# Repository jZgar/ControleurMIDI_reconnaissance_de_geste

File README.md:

# ControleurMIDI_reconnaissance_de_geste
Projet de deuxième année - ENSEA

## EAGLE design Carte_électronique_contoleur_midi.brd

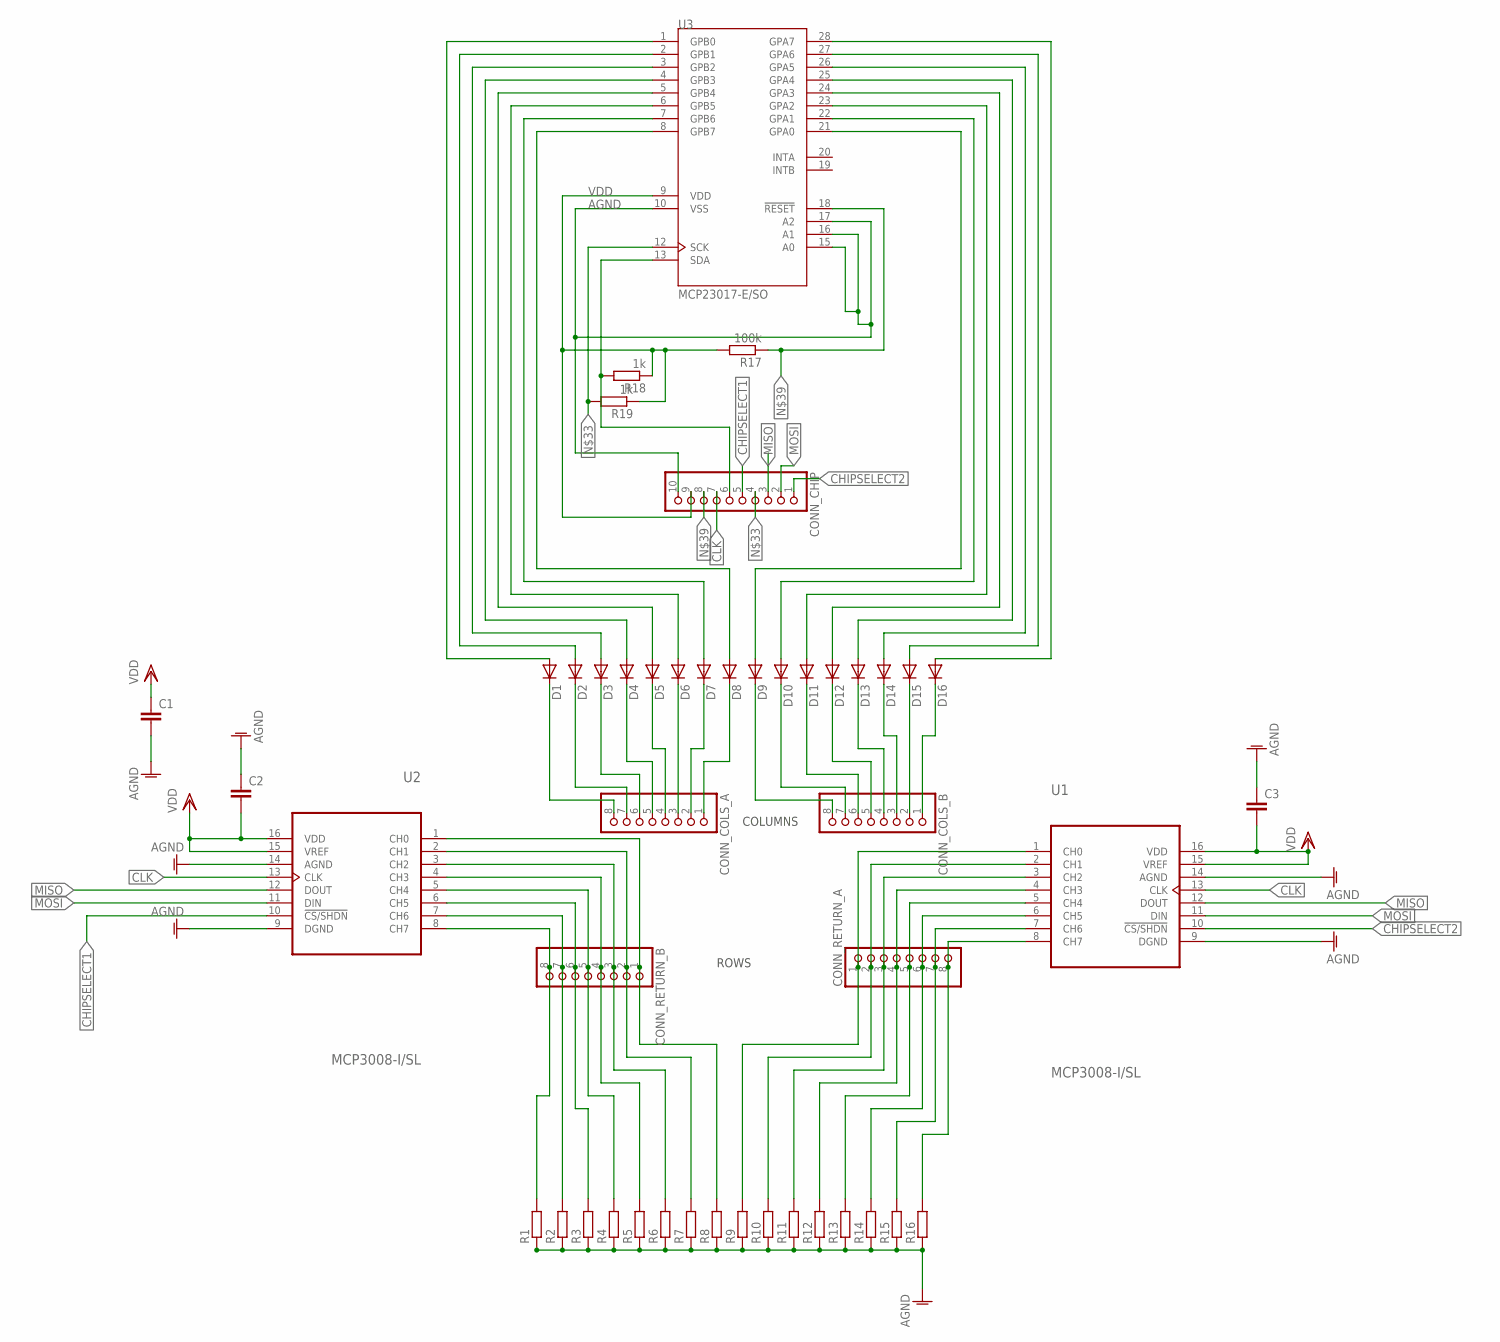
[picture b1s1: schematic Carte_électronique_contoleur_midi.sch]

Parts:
C1, C2, C3: C-EUC1206K; C1206K
CONN_CHIP: PINHD-1X10/90; 1X10/90
CONN_COLS_A: PINHD-1X8/90; 1X08/90
CONN_COLS_B: PINHD-1X8/90; 1X08/90
CONN_RETURN_A: PINHD-1X8/90; 1X08/90
CONN_RETURN_B: PINHD-1X8/90; 1X08/90
D1, D2, D3, D4, D5, D6, D7, D8, D9, D10, D11, D12, D13, D14, D15, D16: DIODE-SOD323-W; SOD323-W
R1, R2, R3, R4, R5, R6, R7, R8, R9, R10, R11, R12, R13, R14, R15, R16: R-EU_M1206; M1206
R17: 100k; M1206
R18, R19: 1k; M1206
U1, U2: MCP3008-I/SL; SOIC127P600X175-16N
U3: MCP23017-E/SO; SOIC127P1030X265-28N

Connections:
AGND: C1.2, C2.1, C3.1, CONN_CHIP.10, R1.1, R2.1, R3.1, R4.1, R5.1, R6.1, R7.1, R8.1, R9.1, R10.1, R11.1, R12.1, R13.1, R14.1, R15.1, R16.1, U1.9 (DGND), U1.14 (AGND), U2.9 (DGND), U2.14 (AGND), U3.10 (VSS), U3.15 (A0), U3.16 (A1), U3.17 (A2)
CHIPSELECT1: CONN_CHIP.5, U2.10 (!CS/SHDN)
CHIPSELECT2: CONN_CHIP.1, U1.10 (!CS/SHDN)
CLK: CONN_CHIP.7, U1.13 (CLK), U2.13 (CLK)
MISO: CONN_CHIP.3, U1.12 (DOUT), U2.12 (DOUT)
MOSI: CONN_CHIP.2, U1.11 (DIN), U2.11 (DIN)
unnamed: D8.A, U3.8 (GPB7)
unnamed: D7.A, U3.7 (GPB6)
unnamed: D6.A, U3.6 (GPB5)
unnamed: D5.A, U3.5 (GPB4)
unnamed: D4.A, U3.4 (GPB3)
unnamed: D3.A, U3.3 (GPB2)
unnamed: D2.A, U3.2 (GPB1)
unnamed: D1.A, U3.1 (GPB0)
unnamed: D9.A, U3.21 (GPA0)
unnamed: D10.A, U3.22 (GPA1)
unnamed: D11.A, U3.23 (GPA2)
unnamed: D12.A, U3.24 (GPA3)
unnamed: D13.A, U3.25 (GPA4)
unnamed: D14.A, U3.26 (GPA5)
unnamed: D15.A, U3.27 (GPA6)
unnamed: D16.A, U3.28 (GPA7)
unnamed: CONN_COLS_A.8, D1.C
unnamed: CONN_COLS_A.7, D2.C
unnamed: CONN_COLS_A.6, D3.C
unnamed: CONN_COLS_A.5, D4.C
unnamed: CONN_COLS_A.4, D5.C
unnamed: CONN_COLS_A.3, D6.C
unnamed: CONN_COLS_A.2, D7.C
unnamed: CONN_COLS_A.1, D8.C
unnamed: CONN_COLS_B.8, D9.C
unnamed: CONN_COLS_B.7, D10.C
unnamed: CONN_COLS_B.6, D11.C
unnamed: CONN_COLS_B.5, D12.C
unnamed: CONN_COLS_B.4, D13.C
unnamed: CONN_COLS_B.3, D14.C
unnamed: CONN_COLS_B.2, D15.C
unnamed: CONN_COLS_B.1, D16.C
unnamed: CONN_CHIP.4, R19.2, U3.12 (SCK)
unnamed: CONN_CHIP.6, R18.2, U3.13 (SDA)
unnamed: CONN_CHIP.8, R17.1, U3.18 (!RESET)
unnamed: CONN_RETURN_B.1, R8.2, U2.1 (CH0)
unnamed: CONN_RETURN_B.2, R7.2, U2.2 (CH1)
unnamed: CONN_RETURN_B.3, R6.2, U2.3 (CH2)
unnamed: CONN_RETURN_B.5, R4.2, U2.5 (CH4)
unnamed: CONN_RETURN_B.6, R3.2, U2.6 (CH5)
unnamed: CONN_RETURN_B.7, R2.2, U2.7 (CH6)
unnamed: CONN_RETURN_B.8, R1.2, U2.8 (CH7)
unnamed: CONN_RETURN_A.2, R10.2, U1.2 (CH1)
unnamed: CONN_RETURN_A.3, R11.2, U1.3 (CH2)
unnamed: CONN_RETURN_A.4, R12.2, U1.4 (CH3)
unnamed: CONN_RETURN_A.1, R9.2, U1.1 (CH0)
unnamed: CONN_RETURN_A.5, R13.2, U1.5 (CH4)
unnamed: CONN_RETURN_A.6, R14.2, U1.6 (CH5)
unnamed: CONN_RETURN_A.7, R15.2, U1.7 (CH6)
unnamed: CONN_RETURN_A.8, R16.2, U1.8 (CH7)
unnamed: CONN_RETURN_B.4, R5.2, U2.4 (CH3)
VDD: C1.1, C2.2, C3.2, CONN_CHIP.9, R17.2, R18.1, R19.1, U1.15 (VREF), U1.16 (VDD), U2.15 (VREF), U2.16 (VDD), U3.9 (VDD)

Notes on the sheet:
COLUMNS
ROWS

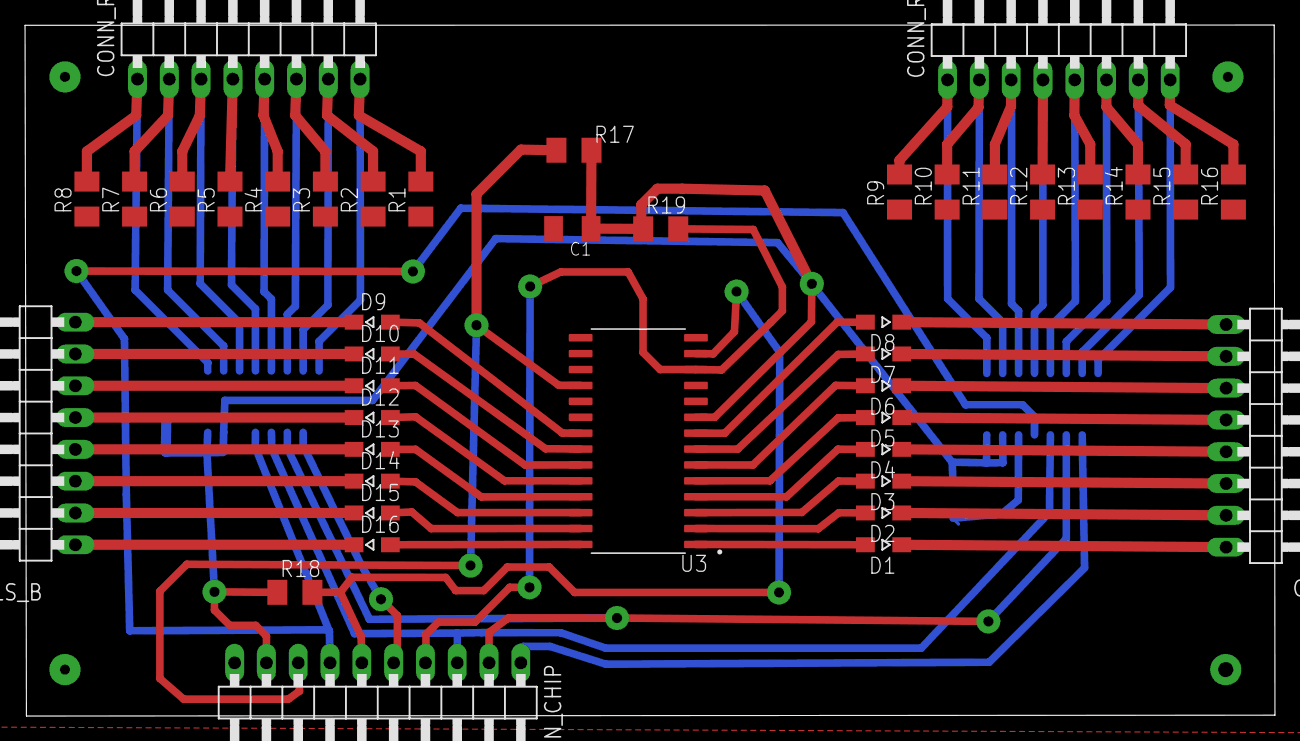
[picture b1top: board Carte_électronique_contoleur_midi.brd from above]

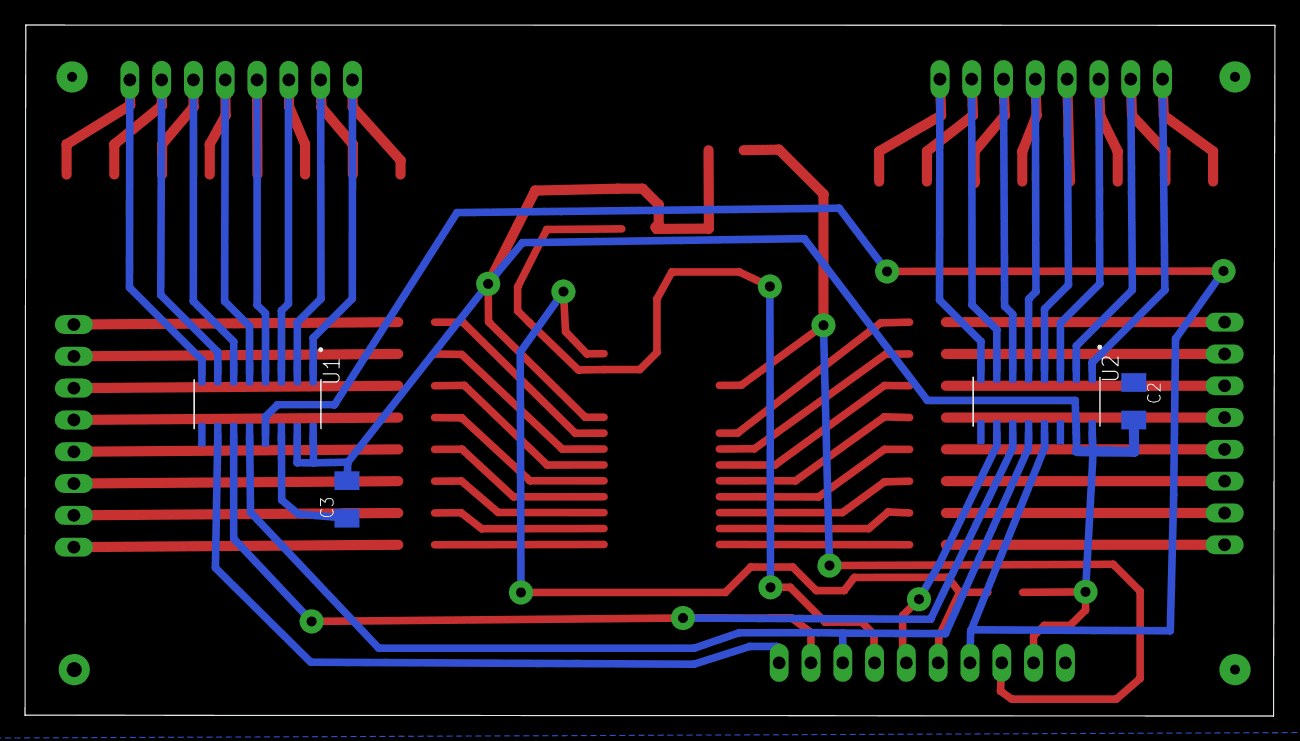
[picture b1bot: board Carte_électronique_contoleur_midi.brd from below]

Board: 2 copper layers, 99.8 x 55.2 mm, 46 parts (4 on the bottom side), 58 nets.

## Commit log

2022-04-22 Create test
2022-04-22 Create controllerMIDI.h5
    IA entraînée
2022-04-22 Update controllermidi_py.py
    Mise à jour du code de la rasb
2022-04-22 Update controllermidi_cnn_py.py
    comments
2022-04-26 Projet complet Cube IDE
2022-04-26 video
2022-04-29 Create Compte_Rendu_Projet_2A.pdf
    CR
2022-04-29 eagle
